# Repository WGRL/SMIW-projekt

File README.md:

Schematy i płytki PCB obejmują 3 projekty:
 - Moduł m5 Stamp-S3, zasilanie 12V i step downy na 5V i 3V3, potrzymanie akumulatorowe i ładowarkę opartą na LM317 + sterowanie źródłem zasilania

 - Moduł czytnika kart micro sd (SPI) i pamięć FRAM

 - Moduł sterowania silnikiem 12V, złącze silnika i enkoder

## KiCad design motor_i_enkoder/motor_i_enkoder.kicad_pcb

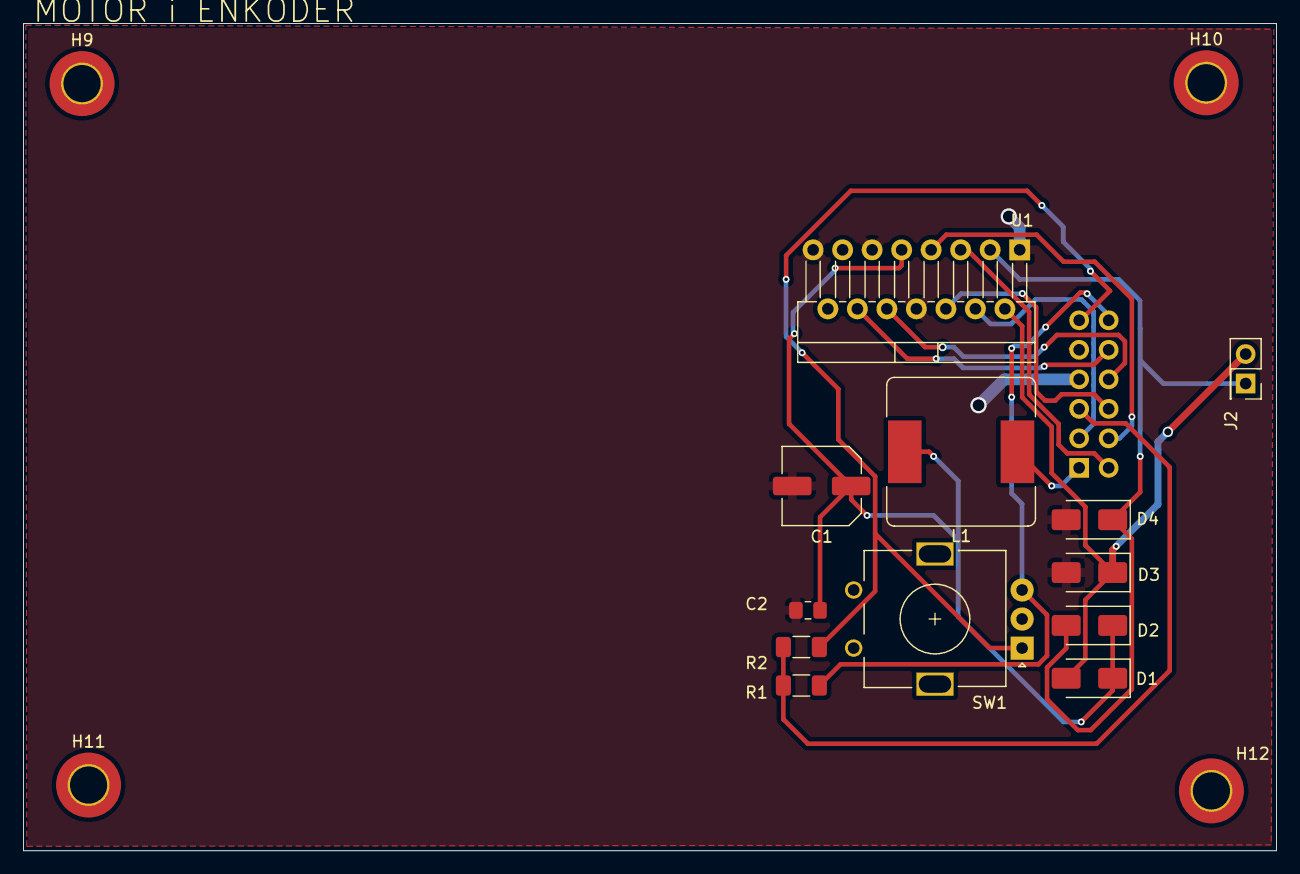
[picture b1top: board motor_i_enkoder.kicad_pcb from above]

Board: 2 copper layers, 107.8 x 71.2 mm, 17 parts (1 on the bottom side), 15 nets.

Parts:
C1: 100uF/16V; C_Elec_6.3x7.7
C2: 100nF; C_0805_2012Metric_Pad1.18x1.45mm_HandSolder
D1, D2, D3, D4: 1N4001; D_SMA
H9, H10, H11, H12: MountingHole; MountingHole_3.2mm_M3_DIN965_Pad_TopBottom
J1: Conn_02x06_Odd_Even; PinHeader_2x06_P2.54mm_Vertical
J2: Conn_02x01; PinSocket_2x01_P2.54mm_Vertical
L1: 1uH; L_Bourns_SRR1260
R1, R2: 1k; R_1206_3216Metric_Pad1.30x1.75mm_HandSolder
SW1: EC11E15204A3; RotaryEncoder_Alps_EC11E_Vertical_H20mm
U1: L298N; TO-220-15_P2.54x5.08mm_StaggerOdd_Lead4.58mm_Vertical

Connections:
12V_2: J1.1, L1.1
/DRIVER_IN1_1: J1.2, U1.5 (IN1)
/DRIVER_IN2_1: J1.4, U1.7 (IN2)
/DRIVER_IN3_1: J1.8, U1.10 (IN3)
/DRIVER_IN4_1: J1.10, U1.12 (IN4)
/ENC_A_1: J1.11, R2.1, SW1.A
/ENC_B_1: J1.12, R1.1, SW1.B
/PWM_A_1: J1.6, U1.6 (EnA)
CPU_GND_2: J1.9, SW1.C
GND_2: C1.2, C2.2, D3.2 (A), D4.2 (A), J1.7, U1.1 (SENSE_A), U1.8 (GND), U1.11 (EnB), U1.15 (SENSE_B)
unnamed: D1.2 (A), D3.1 (K), J2.2, U1.2 (OUT1)
unnamed: C1.1, C2.1, D1.1 (K), D2.1 (K), L1.2, U1.9 (Vss)
unnamed: D2.2 (A), D4.1 (K), J2.1, U1.3 (OUT2)
Vcc_2: J1.3, U1.4 (Vs)
Vdd_2: J1.5, R1.2, R2.2

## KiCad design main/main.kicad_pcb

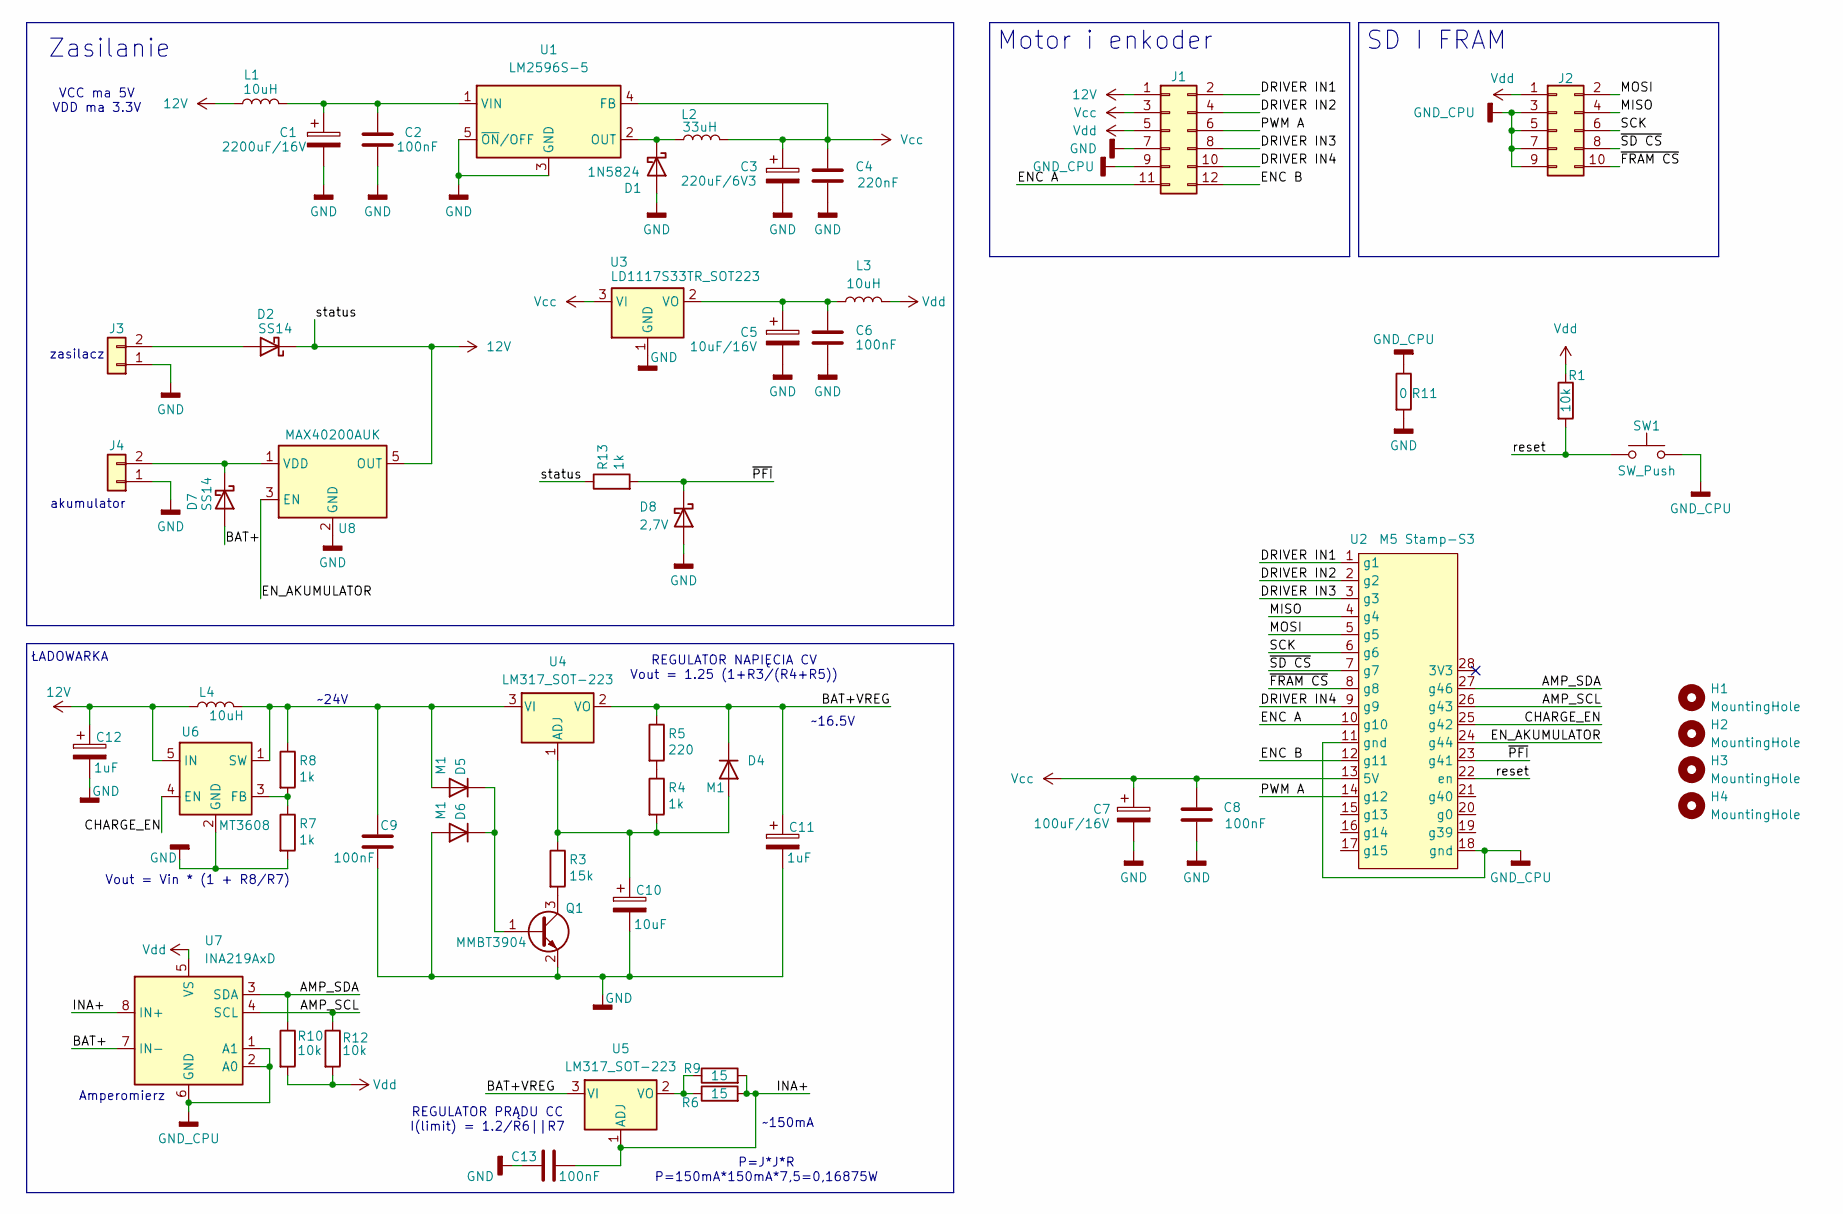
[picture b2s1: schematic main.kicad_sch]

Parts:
C1: 2200uF/16V; CP_Elec_6.3x5.3
C2, C6, C8, C9, C13: 100nF; C_0805_2012Metric_Pad1.18x1.45mm_HandSolder
C3: 220uF/6V3; CP_Elec_6.3x5.3
C4: 220nF; C_0805_2012Metric_Pad1.18x1.45mm_HandSolder
C5: 10uF/16V; CP_Elec_6.3x5.3
C7: 100uF/16V; CP_Elec_6.3x5.3
C10: 10uF; CP_Elec_6.3x5.3
C11, C12: 1uF; CP_Elec_6.3x5.3
D1: 1N5824; D_SMC
D2: SS14; D_SMC
D4, D5, D6: M1; D_SMA
D7: SS14; D_SMA
D8: 2,7V; D_SMA
H1, H2, H3, H4: MountingHole; MountingHole_3.2mm_M3_DIN965_Pad_TopBottom
J1: Conn_02x06_Odd_Even; PinSocket_2x06_P2.54mm_Vertical
J2: Conn_02x05_Odd_Even; PinSocket_2x05_P2.54mm_Vertical_SMD
J3, J4: Conn_01x02; PinSocket_1x02_P1.00mm_Vertical_SMD_Pin1Left
L1, L3, L4: 10uH; L_Bourns_SRR1260
L2: 33uH; L_Bourns_SRR1260
Q1: MMBT3904; SOT-23
R1, R10, R12: 10k; R_1206_3216Metric_Pad1.30x1.75mm_HandSolder
R3: 15k; R_1206_3216Metric_Pad1.30x1.75mm_HandSolder
R4, R7, R8, R13: 1k; R_1206_3216Metric_Pad1.30x1.75mm_HandSolder
R5: 220; R_1206_3216Metric_Pad1.30x1.75mm_HandSolder
R6, R9: 15; R_1206_3216Metric_Pad1.30x1.75mm_HandSolder
R11: 0; R_1206_3216Metric_Pad1.30x1.75mm_HandSolder
SW1: SW_Push; SW_SPST_PTS647_Sx50
U1: LM2596S-5; TO-263-5_TabPin3
U2: M5 Stamp-S3; Stamp-S3-DIP
U3: LD1117S33TR_SOT223; SOT-223-3_TabPin2
U4, U5: LM317_SOT-223; SOT-223-3_TabPin2
U6: MT3608; SOT-23-6
U7: INA219AxD; SOIC-8_3.9x4.9mm_P1.27mm
U8: MAX40200AUK; SOT-23-5

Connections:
12V: C12.1, D2.1 (K), J1.1, L1.1, L4.1, R13.1, U6.5 (IN), U8.5 (OUT)
/AMP_SCL: R12.1, U2.26 (g43), U7.4 (SCL)
/AMP_SDA: R10.1, U2.27 (g46), U7.3 (SDA)
/BAT+: D7.2 (A), U7.7 (IN-)
/BAT+VREG: C11.1, D4.1 (K), R5.1, U4.2 (VO), U5.3 (VI)
/CHARGE_EN: U2.25 (g42), U6.4 (EN)
/DRIVER IN1: J1.2, U2.1 (g1)
/DRIVER IN2: J1.4, U2.2 (g2)
/DRIVER IN3: J1.8, U2.3 (g3)
/DRIVER IN4: J1.10, U2.9 (g9)
/ENC A: J1.11, U2.10 (g10)
/ENC B: J1.12, U2.12 (g11)
/EN_AKUMULATOR: U2.24 (g44), U8.3 (EN)
/INA+: C13.2, R6.2, R9.2, U5.1 (ADJ), U7.8 (IN+)
/MISO: J2.4, U2.4 (g4)
/MOSI: J2.2, U2.5 (g5)
/PWM A: J1.6, U2.14 (g12)
/SCK: J2.6, U2.6 (g6)
/reset: R1.2, SW1.1, U2.22 (en)
/~FRAM CS: J2.10, U2.8 (g8)
/~PFI: D8.1 (K), R13.2, U2.23 (g41)
/~SD CS: J2.8, U2.7 (g7)
GND: C1.2, C2.1, C3.2, C4.2, C5.2, C6.2, C7.2, C8.1, C9.2, C10.2, C11.2, C12.2, C13.1, D1.2 (A), D6.2 (A), D8.2 (A), J1.7, J3.1, J4.1, Q1.2 (E), R7.2, R11.2, U1.3 (GND), U1.5 (~ON/OFF), U3.1 (GND), U6.2 (GND), U8.2 (GND)
GND_CPU: J1.9, J2.3, J2.5, J2.7, J2.9, R11.1, SW1.2, U2.11 (gnd), U2.18 (gnd), U7.1 (A1), U7.2 (A0), U7.6 (GND)
unnamed: D1.1 (K), L2.1, U1.2 (OUT)
unnamed: D2.2 (A), J3.2
unnamed: C10.1, D4.2 (A), R3.1, R4.2, U4.1 (ADJ)
unnamed: C9.1, D5.2 (A), L4.2, R8.1, U4.3 (VI), U6.1 (SW)
unnamed: D5.1 (K), D6.1 (K), Q1.1 (B)
unnamed: D7.1 (K), J4.2, U8.1 (VDD)
unnamed: Q1.3 (C), R3.2
unnamed: R4.1, R5.2
unnamed: C1.1, C2.2, L1.2, U1.1 (VIN)
unnamed: C5.1, C6.1, L3.1, U3.2 (VO)
unnamed: R6.1, R9.1, U5.2 (VO)
unnamed: R7.1, R8.2, U6.3 (FB)
Vcc: C3.1, C4.1, C7.1, C8.2, J1.3, L2.2, U1.4 (FB), U2.13 (5V), U3.3 (VI)
Vdd: J1.5, J2.1, L3.2, R1.1, R10.2, R12.2, U7.5 (VS)

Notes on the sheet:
ŁADOWARKA
zasilacz
REGULATOR NAPIĘCIA CV Vout = 1.25 (1+R3/(R4+R5))
Vout = Vin * (1 + R8/R7)
akumulator
REGULATOR PRĄDU CC I(limit) = 1.2/R6||R7
VCC ma 5V VDD ma 3.3V
Zasilanie
~24V
~150mA
Amperomierz
P=J*J*R P=150mA*150mA*7,5=0,16875W
~16.5V
Motor i enkoder
SD I FRAM

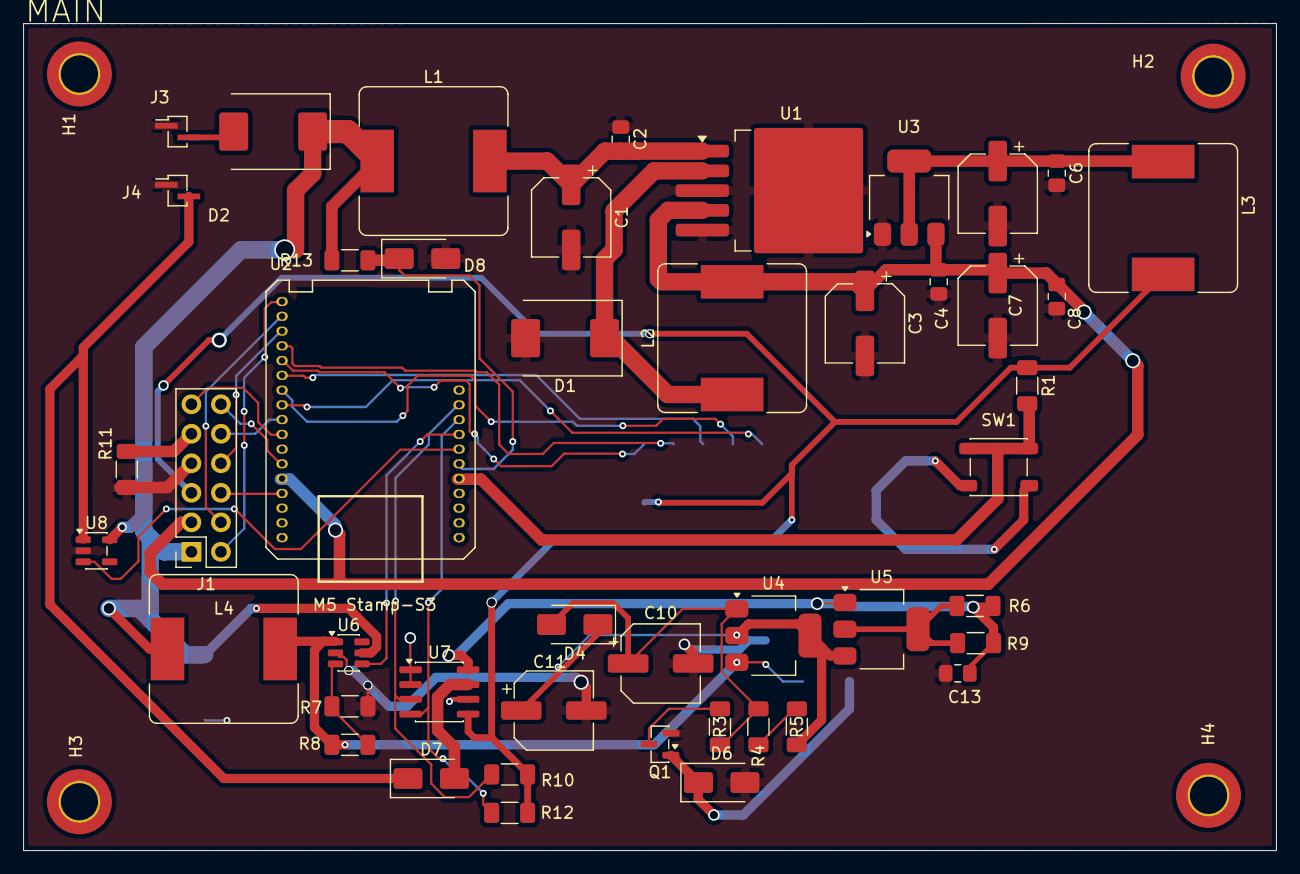
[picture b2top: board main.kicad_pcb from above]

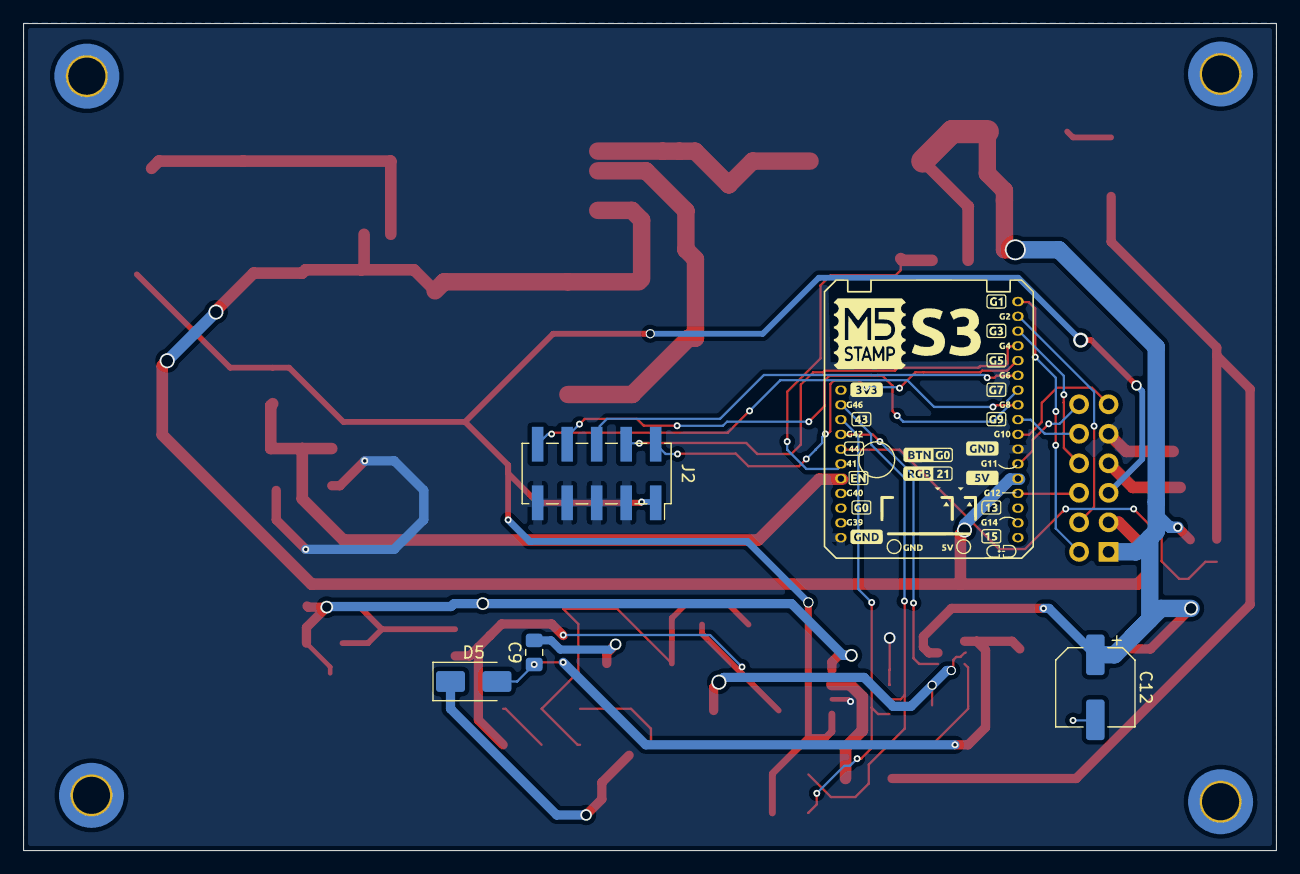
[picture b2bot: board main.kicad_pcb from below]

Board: 2 copper layers, 107.8 x 71.2 mm, 54 parts (4 on the bottom side), 38 nets.

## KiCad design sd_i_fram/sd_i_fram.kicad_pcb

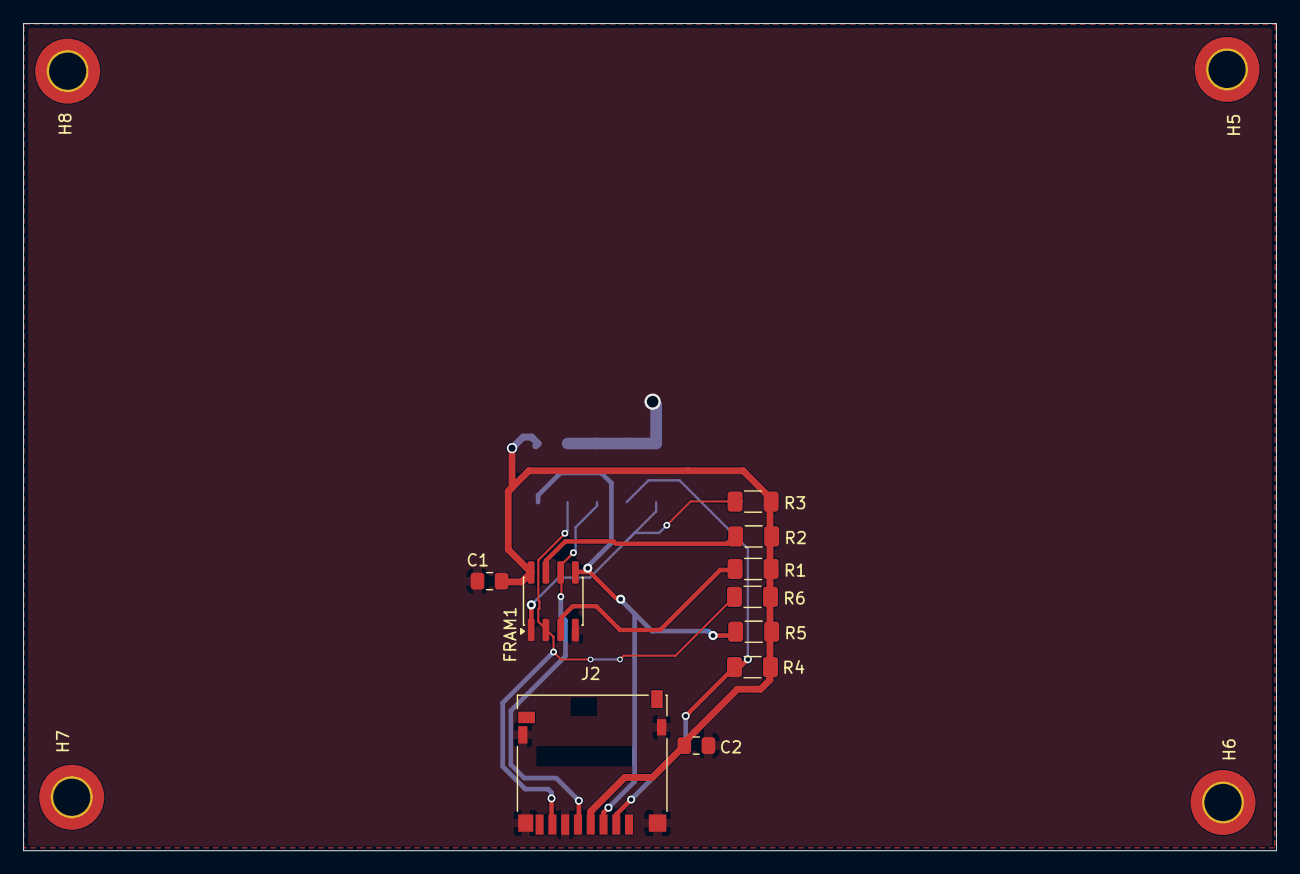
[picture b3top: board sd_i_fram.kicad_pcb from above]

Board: 2 copper layers, 107.9 x 71.2 mm, 15 parts (1 on the bottom side), 9 nets.

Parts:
C1, C2: 100nF; C_0805_2012Metric_Pad1.18x1.45mm_HandSolder
FRAM1: CY15B104Q; SOIC-8_3.9x4.9mm_P1.27mm
H5, H6, H7, H8: MountingHole; MountingHole_3.2mm_M3_DIN965_Pad_TopBottom
J1: Conn_02x05_Odd_Even; PinHeader_2x05_P2.54mm_Vertical_SMD
J2: Molex 104031; microSD_HC_Hirose_DM3D-SF
R1, R2, R3, R4, R5, R6: 10k; R_1206_3216Metric_Pad1.30x1.75mm_HandSolder

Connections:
/MISO_2: FRAM1.2 (SO), J1.4, J2.7 (DAT0), R6.2
/MOSI_2: FRAM1.5 (SI), J1.2, J2.3 (CMD), R5.2
/SCK_2: FRAM1.6 (SCK), J1.6, J2.5 (CLK)
/~FRAM_CS_2: FRAM1.1 (~CS), J1.10, R3.2
/~SD_CS_2: J1.8, J2.2 (DAT3/CD), R4.2
GND_CPU_1: C1.1, C2.2, FRAM1.4 (V_{SS}), J1.3, J1.5, J1.7, J1.9, J2.6 (VSS), J2.SH (SHIELD)
unnamed: FRAM1.7 (~HOLD), R2.2
unnamed: FRAM1.3 (~WP), R1.2
VDD_1: C1.2, C2.1, FRAM1.8 (V_{CC}), J1.1, J2.4 (VDD), R1.1, R2.1, R3.1, R4.1, R5.1, R6.1

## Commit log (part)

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2026-06-13 Skończone ale można zbierać informacje o dalszych szczegółach
2026-06-14 pcb dobrze zdaniem michala (to nie ma sensu)
2026-06-14 rezystor
2026-06-14 Niedziela
2026-06-14 wszystko powinno dzialac. Trzeba zrobic podzial
2026-06-14 foldery
2026-06-25 poprawione pcb. Dodana poprawka w silniku po konsultacjach
2026-06-30 resized. Kanapka
